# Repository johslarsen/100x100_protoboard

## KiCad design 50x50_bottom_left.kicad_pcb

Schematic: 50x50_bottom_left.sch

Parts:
C1: u33
C2: u1
CON1: BARREL_JACK
F1, F2: FUSE
GND1, GND3: INTERCONNECT_1X16
GND2, GND4: INTERCONNECT_1X07
J1, J2, J3, J4, J5, J6, J7, J8, J9, J10, J11, J12, J13, J14, J15, J16, J17, J18, J19, J20, J21, J22, J23, J24, J25, J26, J27, J28, J29, J30, J31, J32, J33, J34, J35, J36, J37, J38, J39, J40, J41, J42, J43, J44, J45, J46, J47, J48, J49, J50, J51, J52, J53, J54, J55, J56, J57, J58, J59, J60, J61, J62, J63, J64: INTERCONNECT_1X03
J65: INTERCONNECT_1X02
JP1, JP2, JP3, JP4, JP5, JP6: JUMPER
JP7, JP8, JP9, JP10, JP11, JP12, JP13, JP14, JP15: JUMPER
P1, P2: CONN_6X2
U1: LM7805CT; TO-220
VCC1: INTERCONNECT_1X16
VDD1: INTERCONNECT_1X16
VIN1: CONN_2
VIN2: CONN_6
VIN_78XX1: CONN_2
VOUT_78XX1: CONN_6

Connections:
unnamed: C1.1, JP2.2, U1.1 (IN), VIN_78XX1.1, VIN_78XX1.2 (PM)
unnamed: C1.2, C2.2, GND1.1, GND2.1, GND3.1, GND4.1, JP7.2, JP8.1, JP10.1, JP12.1, JP15.1, U1.2 (GND)
unnamed: C2.1, JP6.2, JP13.1, U1.3 (OUT), VOUT_78XX1.1, VOUT_78XX1.2, VOUT_78XX1.3, VOUT_78XX1.4, VOUT_78XX1.5, VOUT_78XX1.6
unnamed: CON1.1, F1.1, F2.1, JP1.1
unnamed: CON1.2, JP7.1
unnamed: CON1.3, J65.1
unnamed: F1.2, F2.2, JP1.2, JP2.1, JP3.1
unnamed: JP4.1, JP9.1, VCC1.1
unnamed: JP5.1, JP11.1, VDD1.1
unnamed: JP3.2, JP4.2, JP5.2, JP6.1, JP14.1, VIN1.1, VIN1.2 (PM), VIN2.1, VIN2.2, VIN2.3, VIN2.4, VIN2.5, VIN2.6
unnamed: P1.1, P2.1
unnamed: P1.2, P2.2
unnamed: P1.3, P2.3
unnamed: P1.4, P2.4
unnamed: P1.5, P2.5
unnamed: P1.6, P2.6
unnamed: P1.7, P2.7
unnamed: P1.8, P2.8
unnamed: P1.9, P2.9
unnamed: P1.10, P2.10
unnamed: P1.11, P2.11
unnamed: P1.12, P2.12
unnamed: P1.13, P2.13
unnamed: P1.14, P2.14
unnamed: P1.15, P2.15
unnamed: P1.16, P2.16

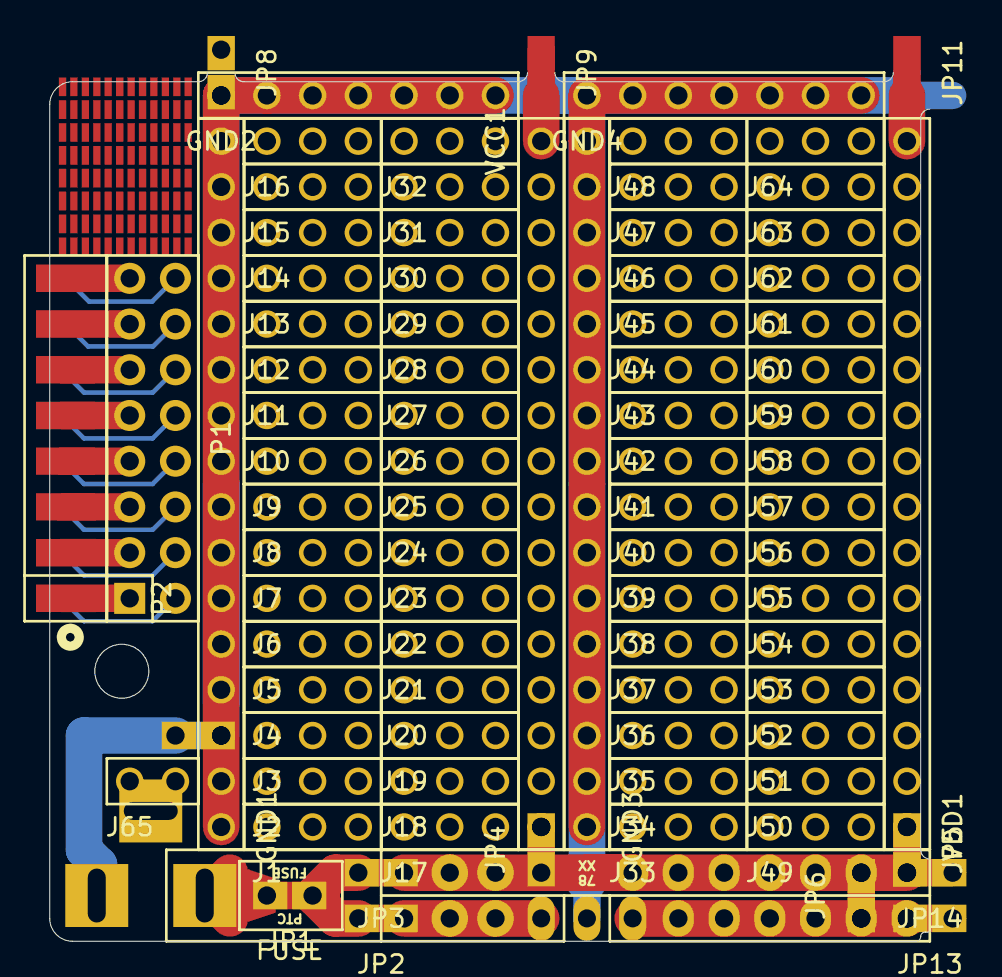
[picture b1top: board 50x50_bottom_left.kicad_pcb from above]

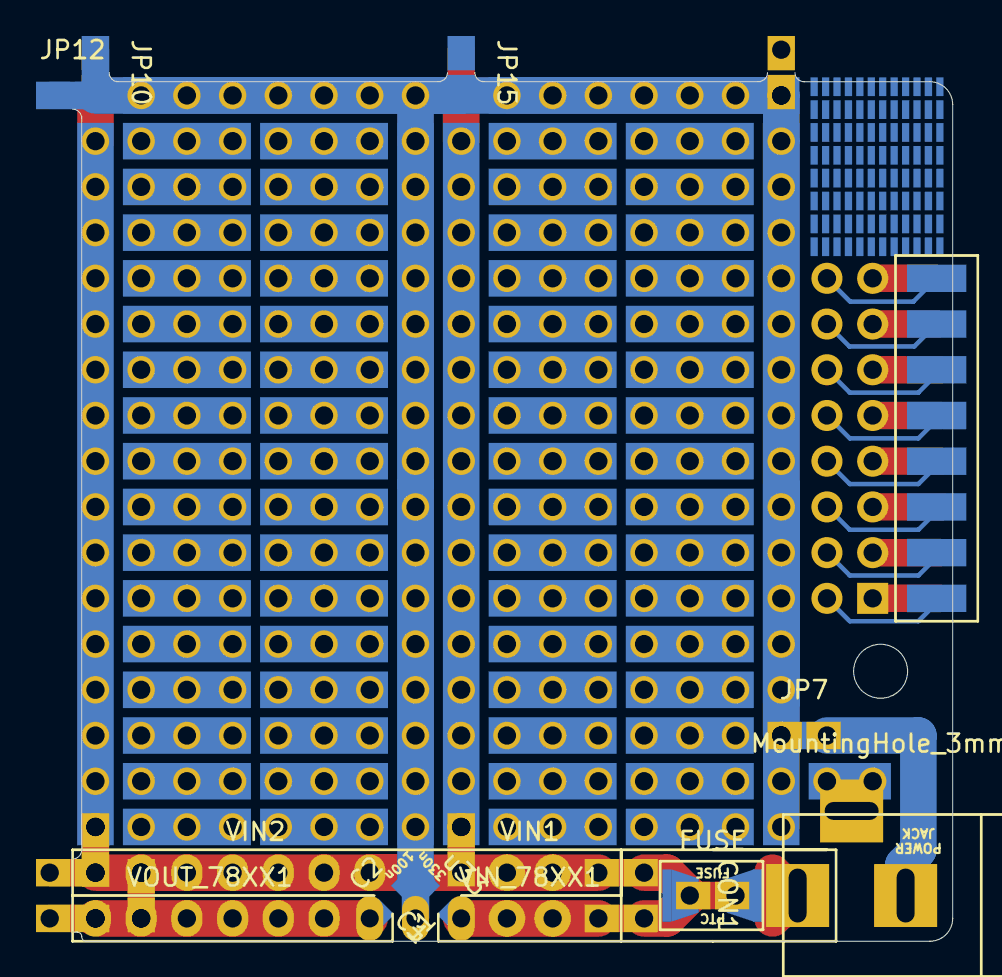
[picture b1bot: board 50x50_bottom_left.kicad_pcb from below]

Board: 2 copper layers, 48.9 x 48.3 mm, 103 parts (16 on the bottom side), 26 nets.

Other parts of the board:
MountingHole_3mm: VAL**; MountingHole_3mm
Ref**: Val**; SMD_127_065_grid_4X12
Ref**#2, Ref**#3, Ref**#4: Val**; SMD_127_065_grid_4X12

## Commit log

2015-05-08 renamed original project to the top-left quadrant of this project
2015-05-08 completed top-left corner
2015-05-08 completed top-right corner
2015-05-08 added empty composite project
2015-05-08 flipped top-right corner and fixed its consequences
2015-05-08 fixed exposed frontside copper for GND traces
2015-05-08 completed first beta-version of the composite board
2015-05-09 moved shorted inter-board GND connection to center, switched av from Oddities:NetTie-I_Connected_SMD because they were asymmetrical and fixed pin header outlines
2015-05-09 renamed top-right corner to bottom-left to reduce the number of rotationes needed to create the composite board
2015-05-09 increased pad size for SMD grid on bottom-left quarter
2015-05-09 increased .1" edge connector from 2*6 to 2*8 to account for the A-100 system bus used in modular synthesizers
2015-05-28 flipped the outermost power rail solder jumper, so that all of these solder-jumpers are shorted on the front
2015-05-28 rounded some corners
2015-05-28 increased the size of 78XX capacitor values, so that they are readable and flipped 78XX text on bottom left so that it does not conflict with capacitor pads
2015-05-31 added v0.5 gerbers
2015-05-31 added 3*3 mouse bites between the sub-boards on both edges
2015-07-05 Revert "added 3*3 mouse bites between the sub-boards on both edges"
    This reverts commit 72bb31031476af87d888838294cc72f0395ed406.
    it turns out that mouse bites shorts the rails if the board house does
    not adhere to the NPTH drill directions, which kind of makes up for the
    usefulness that the mouse bites provided. and they did not improve the
    board sturdiness significantly, so it is not a problem to remove them.
2016-06-29 fp-lib-table: updated to github libraries
2016-06-29 remove center border outline, because drilling it plated shorts PWR and GND
